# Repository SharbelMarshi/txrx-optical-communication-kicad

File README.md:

# A Free Space Optical Communication
This project implements a free-space optical communication link using two separate KiCad-designed boards: a transmitter and a receiver. The transmitter uses an RP2354A microcontroller to frame arbitrary digital payloads into packets and generate $100 \mathrm{kbit/s}$ RZ-OOK modulation for a $650 \mathrm{nm}$ laser module through a level-shifting buffer and an independent hardware safety chain.
The receiver uses a BPW34 photodiode, OPA320 transimpedance amplifier, and TLV3201 comparator to recover the optical pulses and feed them into an RP2354A for decoding, CRC verification, and delivery to the host system.
Both boards include USB-C, UART, SWD, a local $12 \mathrm{MHz}$ crystal, and a $10 \mathrm{MHz}$ SiTime SiT5346 DCTCXO reference. The SiT5346 is connected to the RP2354A through a GPIO/PIO clock input and is controllable over the existing $\text{I²C}$ bus. Each board also exposes a dedicated $1\mathrm{PPS}$ output generated by the RP2354A. The initial target is a stable free-space optical link over approximately $5$ meters.

## Architecture
Two separate $4$ layer boards:
- TX: RP2354A + USB-C + host I/O + $12 \mathrm{MHz}$ crystal + $10 \mathrm{MHz}$ SiT5346 DCTCXO + dedicated $1\mathrm{PPS}$ output + laser driver/safety chain + laser module.
- RX: RP2354A + USB-C + host I/O + $12 \mathrm{MHz}$ crystal + $10 \mathrm{MHz}$ SiT5346 DCTCXO + dedicated $1\mathrm{PPS}$ output + BPW34 / OPA320 / TLV3201 optical receiver + ADC monitor.

### TX
- TX_ROOT
- TX_POWER_USB
- TX_MCU_CLOCK
- TX_HOST_IO
- TX_LASER

### RX
- RX_ROOT
- RX_POWER_USB
- RX_MCU_CLOCK
- RX_HOST_IO
- RX_OPTICAL_AFE
- RX_MONITOR

### TX schamtics:

### TX PCB: 

### RX schamtics:

### RX PCB: 

## Library:
### Pre-built Components Compatibility Verfication:

Verified: Symbol and Footprint compatibility: 

1. RP2354A  ✓
2. AP2112K-3.3  ✓
3. SN74AHCT1G125DBVR  ✓
4. TPS22919DCKR  ✓
5. USBLC6-2SC6  ✓
7. REF2033  ✓

### Costum Components:

1. SiT5346 ✓
2. OPA320  ✓
3. TLV3201 ✓
4. BPW34 (custom footprint)  ✓
5. TPS7A2033  (customed symbol) ✓
6. ABM8-272-T3_3225 (custom footprint)  ✓
7. AOTA-B201610S3R3-101-T (custom footprint) ✓
8. ES22MCBE (custom footprint) ✓
9. B3B-PH-K-S ✓
10. B8B-PH-K-S ✓
11. ARD-LASER-MDI650-1-5 ✓
12. FTSH-105-01-L-DV-K ✓
13. USB4105-GF-A ✓

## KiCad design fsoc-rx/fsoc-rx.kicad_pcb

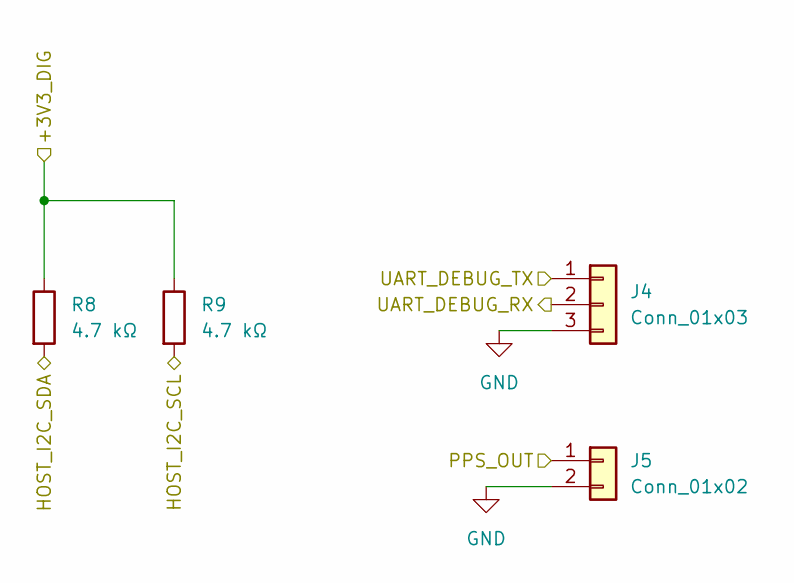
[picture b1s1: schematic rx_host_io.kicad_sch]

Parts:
J4: Conn_01x03; PinHeader_1x03_P2.54mm_Vertical
J5: Conn_01x02; PinHeader_1x02_P2.54mm_Vertical
R8, R9: 4.7 kΩ; R_0603_1608Metric

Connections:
/+3V3_DIG: R8.1, R9.1; also elsewhere on the board
/HOST_I2C_SCL: R9.2; also elsewhere on the board
/HOST_I2C_SDA: R8.2; also elsewhere on the board
/PPS_OUT: J5.1; also elsewhere on the board
/UART_DEBUG_RX: J4.2; also elsewhere on the board
/UART_DEBUG_TX: J4.1; also elsewhere on the board
GND: J4.3, J5.2; also elsewhere on the board

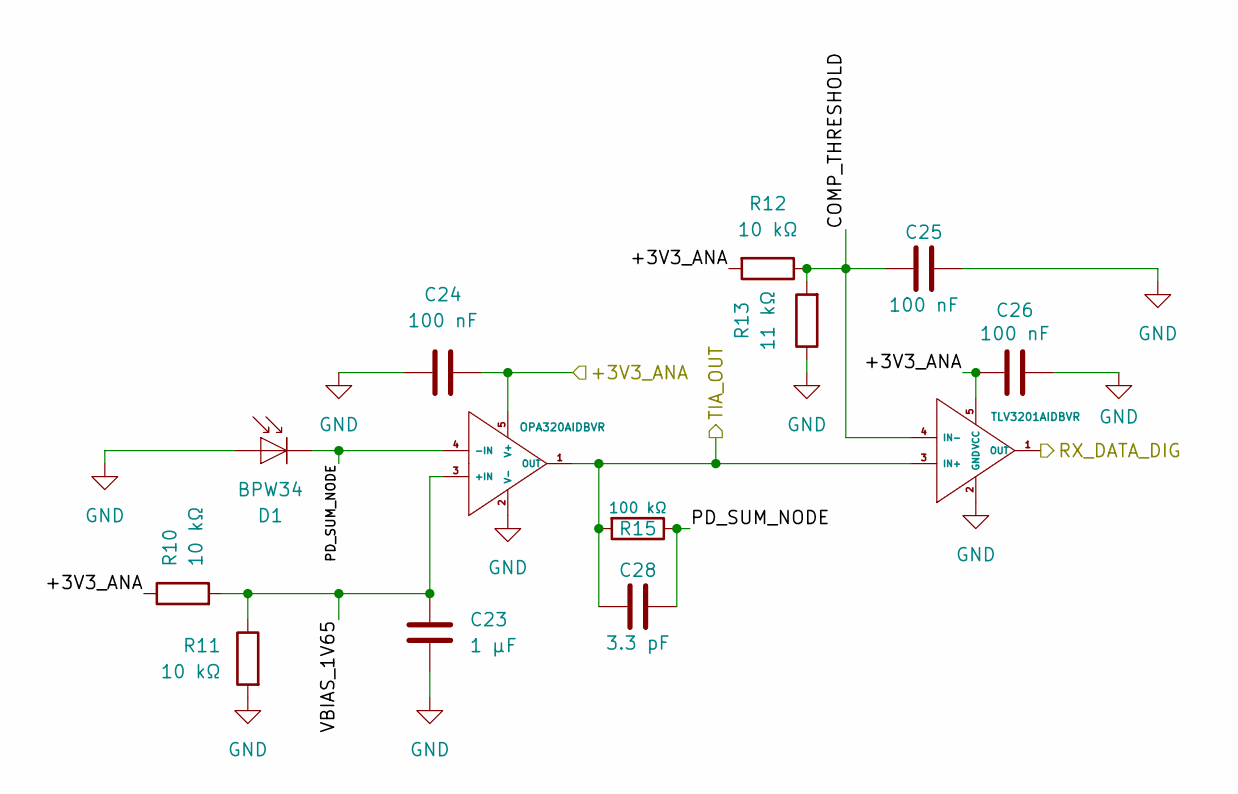
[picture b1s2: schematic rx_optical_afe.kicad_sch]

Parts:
C23: 1 µF; C_0805_2012Metric
C24, C25, C26: 100 nF; C_0603_1608Metric
C28: 3.3 pF; C_0603_1608Metric
D1: BPW34; BPW34_Vishay; MPN BPW34
R10, R11, R12: 10 kΩ; R_0603_1608Metric
R13: 11 kΩ; R_0603_1608Metric
R15: 100 kΩ; R_0603_1608Metric
U5: OPA320AIDBVR; SOT-23-5; MPN OPA320AIDBVR
U6: TLV3201AIDBVR; SOT-23-5; MPN TLV3201AIDBVR

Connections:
/+3V3_ANA: C24.2, C26.2, R10.1, R12.2, U5.5 (V+), U6.5 (VCC); also elsewhere on the board
/RX_DATA_DIG: U6.1 (OUT); also elsewhere on the board
/RX_OPTICAL_AFE/COMP_THRESHOLD: C25.1, R12.1, R13.2, U6.4 (IN-)
/RX_OPTICAL_AFE/PD_SUM_NODE: C28.2, D1.1 (K), R15.1, U5.4 (-IN)
/RX_OPTICAL_AFE/VBIAS_1V65: C23.1, R10.2, R11.1, U5.3 (+IN)
/TIA_OUT: C28.1, R15.2, U5.1 (OUT), U6.3 (IN+); also elsewhere on the board
GND: C23.2, C24.1, C25.2, C26.1, D1.2 (A), R11.2, R13.1, U5.2 (V-), U6.2 (GND); also elsewhere on the board

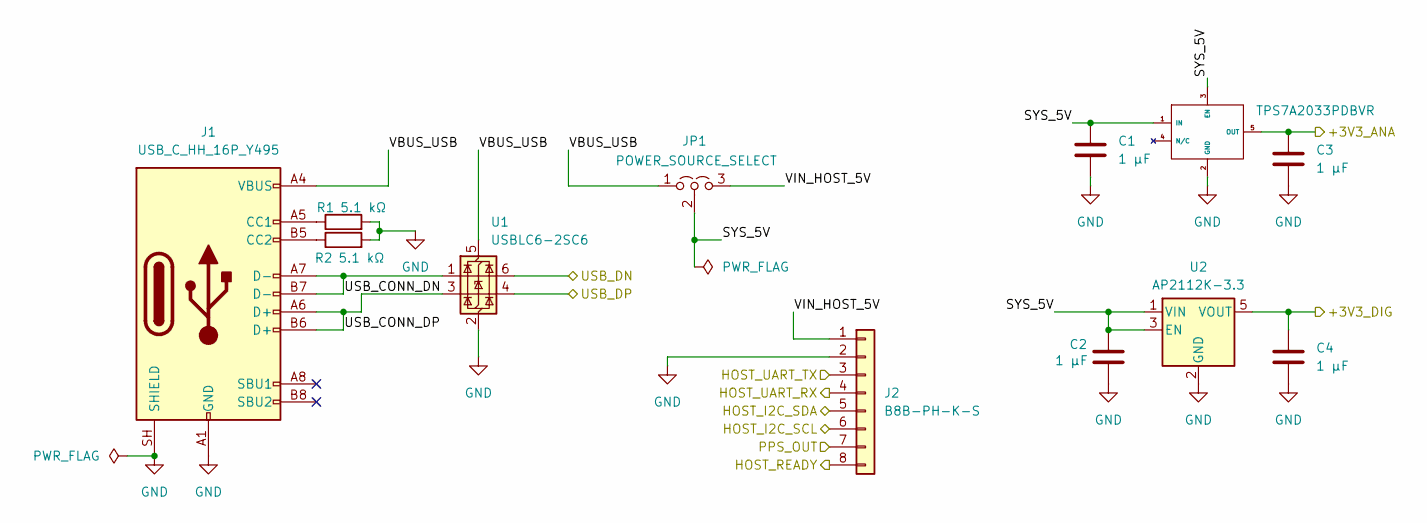
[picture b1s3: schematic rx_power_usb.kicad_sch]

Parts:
C1, C2, C3, C4: 1 µF; C_0805_2012Metric
J1: USB_C_HH_16P_Y495; MPN USB4105-GF-A
J2: B8B-PH-K-S; PinHeader_1x08_P2.54mm_Vertical; MPN B8B-PH-K-S
JP1: POWER_SOURCE_SELECT; PinHeader_1x03_P2.54mm_Vertical; MPN TSW-103-07-G-S
R1, R2: 5.1 kΩ; R_0603_1608Metric
U1: USBLC6-2SC6; SOT-23-6
U2: AP2112K-3.3; SOT-23-5
U3: TPS7A2033PDBVR; SOT-23-5; MPN TPS7A2033PDBVR

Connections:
/+3V3_ANA: C3.1, U3.5 (OUT); also elsewhere on the board
/+3V3_DIG: C4.1, U2.5 (VOUT); also elsewhere on the board
/HOST_I2C_SCL: J2.6; also elsewhere on the board
/HOST_I2C_SDA: J2.5; also elsewhere on the board
/HOST_READY: J2.8; also elsewhere on the board
/HOST_UART_RX: J2.4; also elsewhere on the board
/HOST_UART_TX: J2.3; also elsewhere on the board
/PPS_OUT: J2.7; also elsewhere on the board
/RX_POWER_USB/SYS_5V: C1.1, C2.1, JP1.2 (C), U2.1 (VIN), U2.3 (EN), U3.1 (IN), U3.3 (EN)
/RX_POWER_USB/USB_CONN_DN: J1.A7 (D-), J1.B7 (D-), U1.1 (I/O1)
/RX_POWER_USB/USB_CONN_DP: J1.A6 (D+), J1.B6 (D+), U1.3 (I/O2)
/RX_POWER_USB/VBUS_USB: J1.A4 (VBUS), J1.A9 (VBUS), J1.B4 (VBUS), J1.B9 (VBUS), JP1.1 (A), U1.5 (VBUS)
/RX_POWER_USB/VIN_HOST_5V: J2.1, JP1.3 (B)
/USB_DN: U1.6 (I/O1); also elsewhere on the board
/USB_DP: U1.4 (I/O2); also elsewhere on the board
GND: C1.2, C2.2, C3.2, C4.2, J1.A1 (GND), J1.A12 (GND), J1.B1 (GND), J1.B12 (GND), J1.SH (SHIELD), J2.2, R1.2, R2.2, U1.2 (GND), U2.2 (GND), U3.2 (GND); also elsewhere on the board
unnamed: J1.A5 (CC1), R1.1
unnamed: J1.B5 (CC2), R2.1

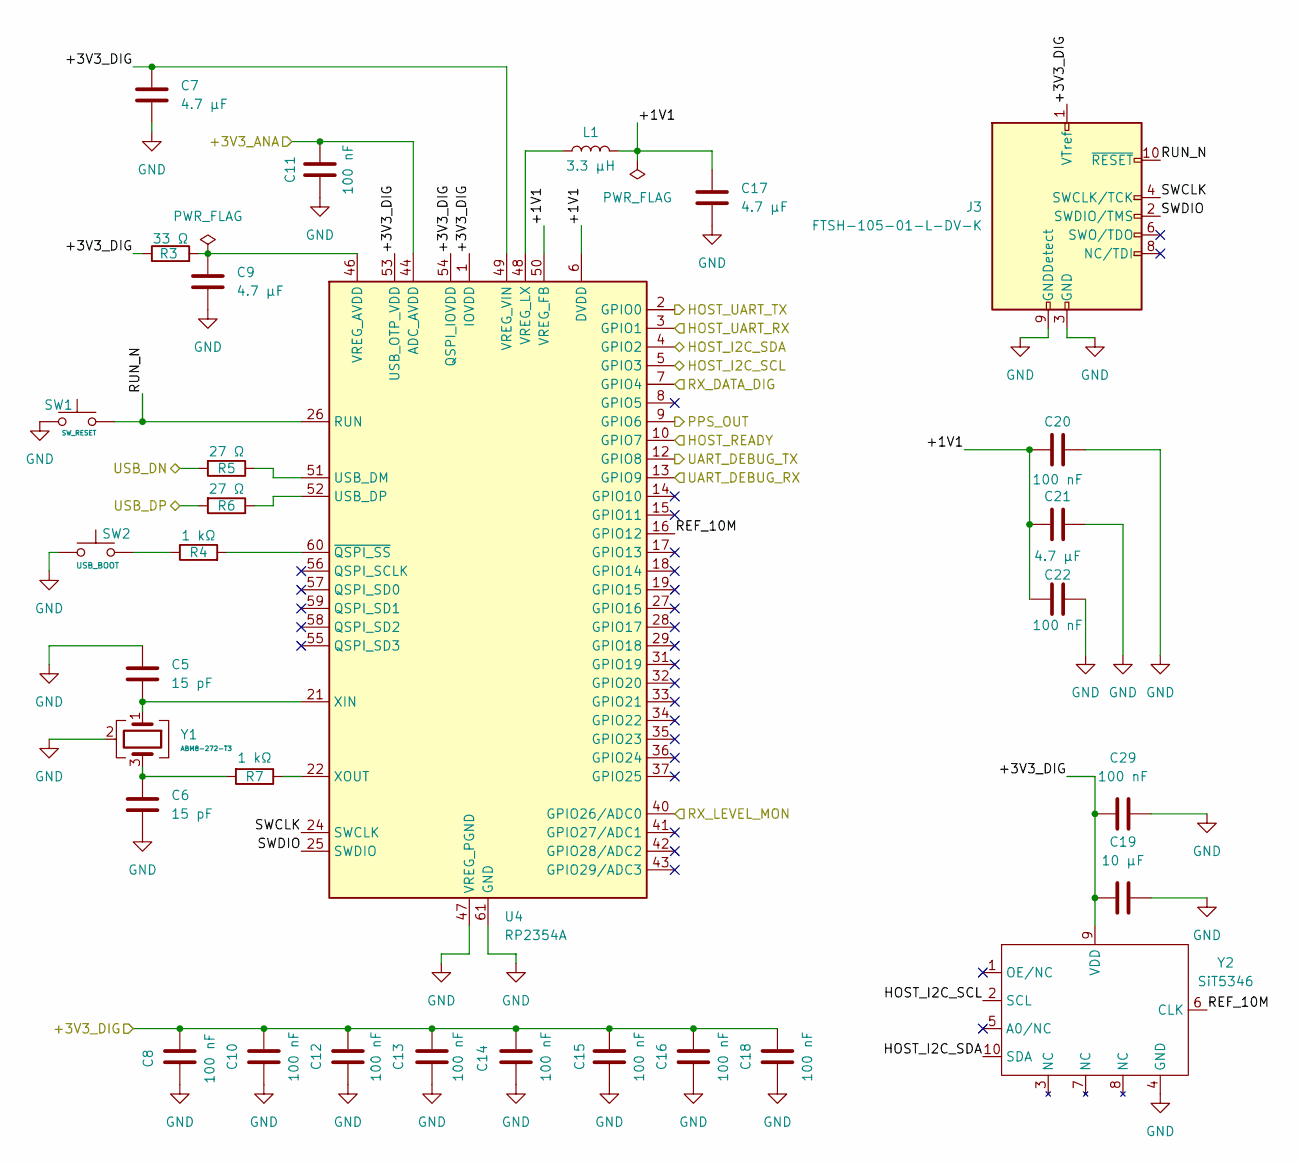
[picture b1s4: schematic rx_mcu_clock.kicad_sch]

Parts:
C5, C6: 15 pF; C_0603_1608Metric
C7, C9, C17, C21: 4.7 µF; C_0805_2012Metric
C8, C10, C11, C12, C13, C14, C15, C16, C18, C20, C22, C29: 100 nF; C_0603_1608Metric
C19: 10 µF; C_0805_2012Metric
J3: FTSH-105-01-L-DV-K; MPN FTSH-105-01-L-DV-K
L1: 3.3 µH; AOTA-B201610S3R3-101-T
R3: 33 Ω; R_0603_1608Metric
R4, R7: 1 kΩ; R_0603_1608Metric
R5, R6: 27 Ω; R_0603_1608Metric
SW1: SW_RESET; SW_SPST_PTS645Sx43SMTR92
SW2: USB_BOOT; SW_SPST_PTS645Sx43SMTR92
U4: RP2354A; RP2354A_ThermalVia_0p30
Y1: ABM8-272-T3; ABM8-272-T3_3225; MPN ABM8-272-T3
Y2: SiT5346; SiT5346_5.0x3.2mm_10L; MPN TBD - SiT5346 10MHz 3.3V LVCMOS DCTCXO; JLCPCB Part TBD - Global Sourcing if not stocked

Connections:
/+3V3_ANA: C11.2, U4.44 (ADC_AVDD); also elsewhere on the board
/+3V3_DIG: C7.1, C8.2, C10.2, C12.2, C13.2, C14.2, C15.2, C16.2, C18.2, C19.1, C29.1, J3.1 (VTref), R3.1, U4.1 (IOVDD), U4.11 (IOVDD), U4.20 (IOVDD), U4.30 (IOVDD), U4.38 (IOVDD), U4.45 (IOVDD), U4.49 (VREG_VIN), U4.53 (USB_OTP_VDD), U4.54 (QSPI_IOVDD), Y2.9 (VDD); also elsewhere on the board
/HOST_I2C_SCL: U4.5 (GPIO3), Y2.2 (SCL); also elsewhere on the board
/HOST_I2C_SDA: U4.4 (GPIO2), Y2.10 (SDA); also elsewhere on the board
/HOST_READY: U4.10 (GPIO7); also elsewhere on the board
/HOST_UART_RX: U4.3 (GPIO1); also elsewhere on the board
/HOST_UART_TX: U4.2 (GPIO0); also elsewhere on the board
/PPS_OUT: U4.9 (GPIO6); also elsewhere on the board
/RX_DATA_DIG: U4.7 (GPIO4); also elsewhere on the board
/RX_LEVEL_MON: U4.40 (GPIO26/ADC0); also elsewhere on the board
/RX_MCU_CLOCK/+1V1: C17.1, C20.1, C21.1, C22.2, L1.2, U4.6 (DVDD), U4.23 (DVDD), U4.39 (DVDD), U4.50 (VREG_FB)
/RX_MCU_CLOCK/REF_10M: U4.16 (GPIO12), Y2.6 (CLK)
/RX_MCU_CLOCK/RUN_N: J3.10 (~RESET), SW1.1, U4.26 (RUN)
/RX_MCU_CLOCK/SWCLK: J3.4 (SWCLK/TCK), U4.24 (SWCLK)
/RX_MCU_CLOCK/SWDIO: J3.2 (SWDIO/TMS), U4.25 (SWDIO)
/UART_DEBUG_RX: U4.13 (GPIO9); also elsewhere on the board
/UART_DEBUG_TX: U4.12 (GPIO8); also elsewhere on the board
/USB_DN: R5.2; also elsewhere on the board
/USB_DP: R6.2; also elsewhere on the board
GND: C5.1, C6.2, C7.2, C8.1, C9.2, C10.1, C11.1, C12.1, C13.1, C14.1, C15.1, C16.1, C17.2, C18.1, C19.2, C20.2, C21.2, C22.1, C29.2, J3.3 (GND), J3.5 (GND), J3.9 (GNDDetect), SW1.2, SW2.1, U4.47 (VREG_PGND), U4.61 (GND), Y1.2 (G), Y1.4 (G), Y2.4 (GND); also elsewhere on the board
unnamed: C6.1, R7.2, Y1.3
unnamed: R4.1, SW2.2
unnamed: R5.1, U4.51 (USB_DM)
unnamed: R6.1, U4.52 (USB_DP)
unnamed: C9.1, R3.2, U4.46 (VREG_AVDD)
unnamed: L1.1, U4.48 (VREG_LX)
unnamed: C5.2, U4.21 (XIN), Y1.1
unnamed: R7.1, U4.22 (XOUT)
unnamed: R4.2, U4.60 (~QSPI_SS)

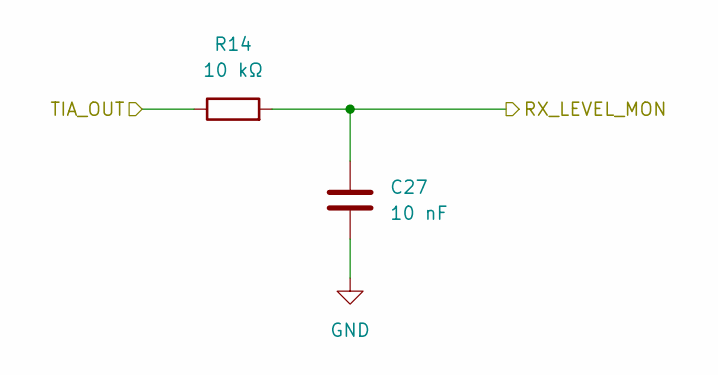
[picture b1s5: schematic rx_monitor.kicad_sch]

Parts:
C27: 10 nF; C_0603_1608Metric
R14: 10 kΩ; R_0603_1608Metric

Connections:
/RX_LEVEL_MON: C27.1, R14.2; also elsewhere on the board
/TIA_OUT: R14.1; also elsewhere on the board
GND: C27.2; also elsewhere on the board

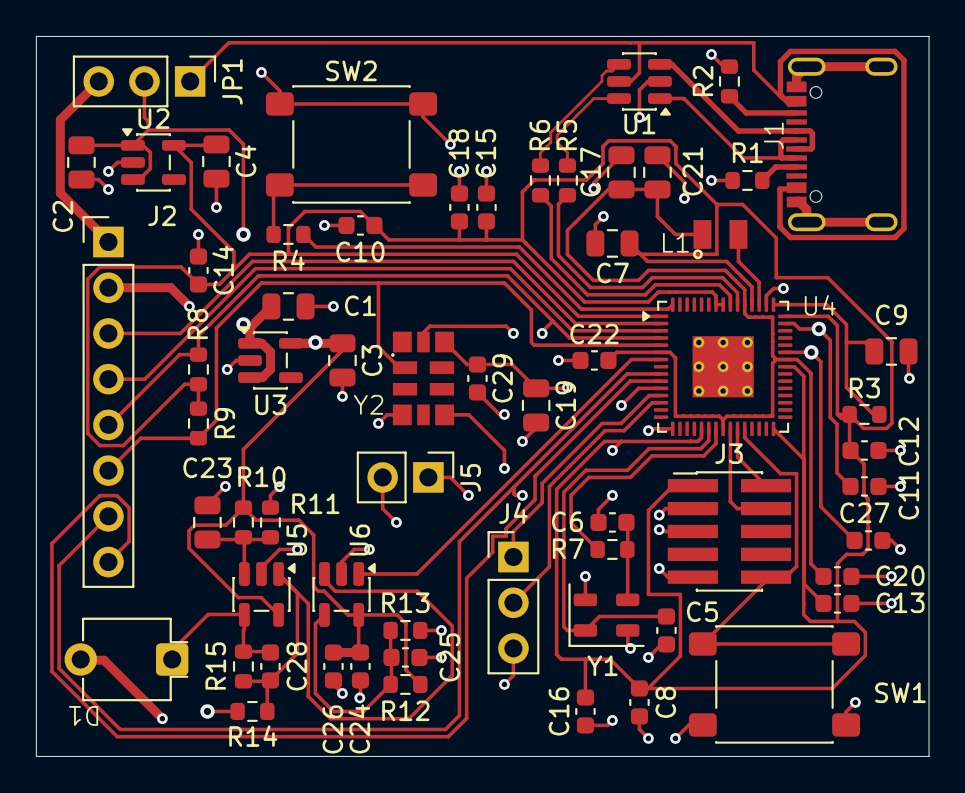
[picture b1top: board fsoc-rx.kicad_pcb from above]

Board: 4 copper layers, 49.6 x 40.0 mm, 62 parts (0 on the bottom side), 40 nets.

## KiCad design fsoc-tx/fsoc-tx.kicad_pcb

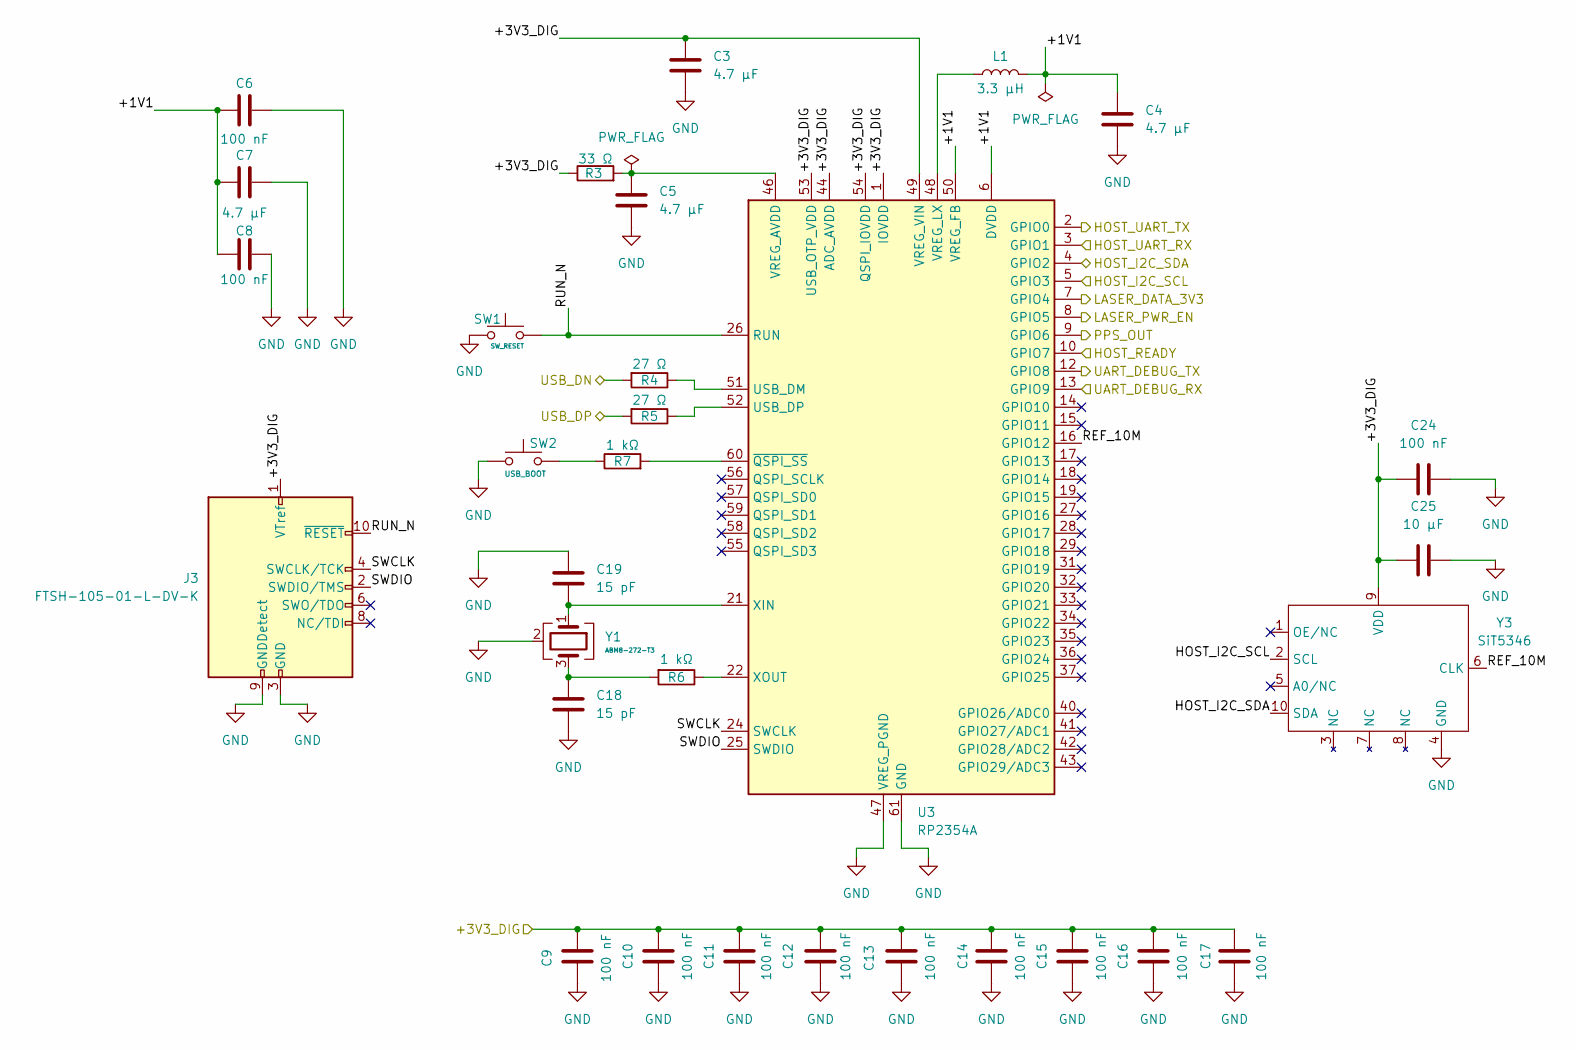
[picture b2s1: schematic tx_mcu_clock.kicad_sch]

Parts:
C3, C4, C5, C7: 4.7 µF; C_0805_2012Metric
C6, C8, C9, C10, C11, C12, C13, C14, C15, C16, C17, C24: 100 nF; C_0603_1608Metric
C18, C19: 15 pF; C_0603_1608Metric
C25: 10 µF; C_0805_2012Metric
J3: FTSH-105-01-L-DV-K; MPN FTSH-105-01-L-DV-K
L1: 3.3 µH; AOTA-B201610S3R3-101-T
R3: 33 Ω; R_0603_1608Metric
R4, R5: 27 Ω; R_0603_1608Metric
R6, R7: 1 kΩ; R_0603_1608Metric
SW1: SW_RESET; SW_SPST_PTS645Sx43SMTR92
SW2: USB_BOOT; SW_SPST_PTS645Sx43SMTR92
U3: RP2354A; RP2354A_ThermalVia_0p30
Y1: ABM8-272-T3; ABM8-272-T3_3225; MPN ABM8-272-T3
Y3: SiT5346; SiT5346_5.0x3.2mm_10L; MPN TBD - SiT5346 10MHz 3.3V LVCMOS DCTCXO; JLCPCB Part TBD - Global Sourcing if not stocked

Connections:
/+3V3_DIG: C3.1, C9.2, C10.2, C11.2, C12.2, C13.2, C14.2, C15.2, C16.2, C17.2, C24.1, C25.1, J3.1 (VTref), R3.1, U3.1 (IOVDD), U3.11 (IOVDD), U3.20 (IOVDD), U3.30 (IOVDD), U3.38 (IOVDD), U3.44 (ADC_AVDD), U3.45 (IOVDD), U3.49 (VREG_VIN), U3.53 (USB_OTP_VDD), U3.54 (QSPI_IOVDD), Y3.9 (VDD); also elsewhere on the board
/HOST_I2C_SCL: U3.5 (GPIO3), Y3.2 (SCL); also elsewhere on the board
/HOST_I2C_SDA: U3.4 (GPIO2), Y3.10 (SDA); also elsewhere on the board
/HOST_READY: U3.10 (GPIO7); also elsewhere on the board
/HOST_UART_RX: U3.3 (GPIO1); also elsewhere on the board
/HOST_UART_TX: U3.2 (GPIO0); also elsewhere on the board
/LASER_DATA_3V3: U3.7 (GPIO4); also elsewhere on the board
/LASER_PWR_EN: U3.8 (GPIO5); also elsewhere on the board
/PPS_OUT: U3.9 (GPIO6); also elsewhere on the board
/TX_MCU_CLOCK/+1V1: C4.1, C6.1, C7.1, C8.2, L1.2, U3.6 (DVDD), U3.23 (DVDD), U3.39 (DVDD), U3.50 (VREG_FB)
/TX_MCU_CLOCK/REF_10M: U3.16 (GPIO12), Y3.6 (CLK)
/TX_MCU_CLOCK/RUN_N: J3.10 (~RESET), SW1.1, U3.26 (RUN)
/TX_MCU_CLOCK/SWCLK: J3.4 (SWCLK/TCK), U3.24 (SWCLK)
/TX_MCU_CLOCK/SWDIO: J3.2 (SWDIO/TMS), U3.25 (SWDIO)
/UART_DEBUG_RX: U3.13 (GPIO9); also elsewhere on the board
/UART_DEBUG_TX: U3.12 (GPIO8); also elsewhere on the board
/USB_DN: R4.2; also elsewhere on the board
/USB_DP: R5.2; also elsewhere on the board
GND: C3.2, C4.2, C5.2, C6.2, C7.2, C8.1, C9.1, C10.1, C11.1, C12.1, C13.1, C14.1, C15.1, C16.1, C17.1, C18.2, C19.1, C24.2, C25.2, J3.3 (GND), J3.5 (GND), J3.9 (GNDDetect), SW1.2, SW2.1, U3.47 (VREG_PGND), U3.61 (GND), Y1.2 (G), Y1.4 (G), Y3.4 (GND); also elsewhere on the board
unnamed: C18.1, R6.2, Y1.3
unnamed: R7.1, SW2.2
unnamed: R4.1, U3.51 (USB_DM)
unnamed: R5.1, U3.52 (USB_DP)
unnamed: C5.1, R3.2, U3.46 (VREG_AVDD)
unnamed: L1.1, U3.48 (VREG_LX)
unnamed: C19.2, U3.21 (XIN), Y1.1
unnamed: R6.1, U3.22 (XOUT)
unnamed: R7.2, U3.60 (~QSPI_SS)

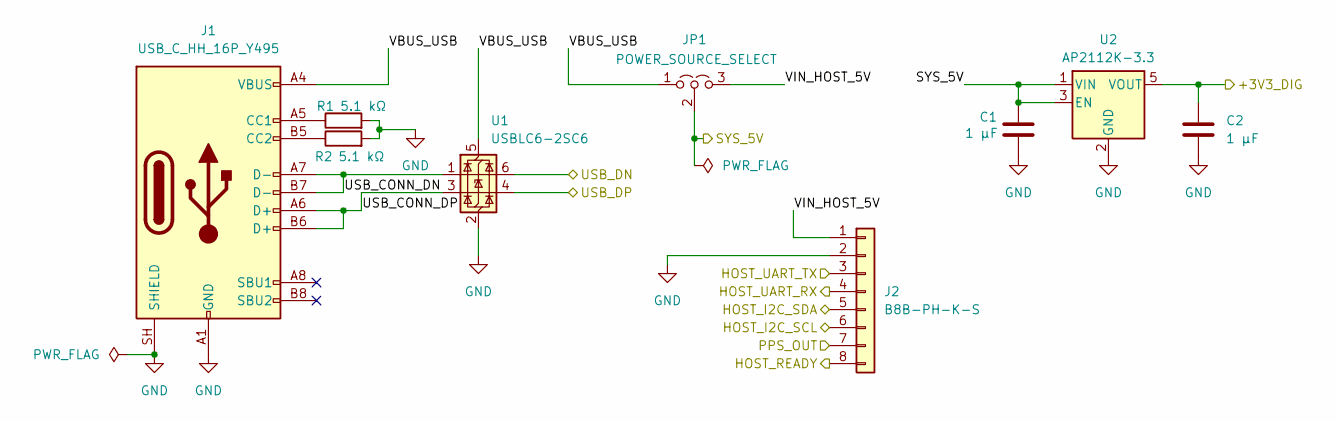
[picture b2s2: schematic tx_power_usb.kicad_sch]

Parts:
C1, C2: 1 µF; C_0805_2012Metric
J1: USB_C_HH_16P_Y495; MPN USB4105-GF-A
J2: B8B-PH-K-S; PinHeader_1x08_P2.54mm_Vertical; MPN B8B-PH-K-S
JP1: POWER_SOURCE_SELECT; PinHeader_1x03_P2.54mm_Vertical; MPN TSW-103-07-G-S
R1, R2: 5.1 kΩ; R_0603_1608Metric
U1: USBLC6-2SC6; SOT-23-6
U2: AP2112K-3.3; SOT-23-5

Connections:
/+3V3_DIG: C2.1, U2.5 (VOUT); also elsewhere on the board
/HOST_I2C_SCL: J2.6; also elsewhere on the board
/HOST_I2C_SDA: J2.5; also elsewhere on the board
/HOST_READY: J2.8; also elsewhere on the board
/HOST_UART_RX: J2.4; also elsewhere on the board
/HOST_UART_TX: J2.3; also elsewhere on the board
/PPS_OUT: J2.7; also elsewhere on the board
/SYS_5V: C1.1, JP1.2 (C), U2.1 (VIN), U2.3 (EN); also elsewhere on the board
/TX_POWER_USB/USB_CONN_DN: J1.A7 (D-), J1.B7 (D-), U1.1 (I/O1)
/TX_POWER_USB/USB_CONN_DP: J1.A6 (D+), J1.B6 (D+), U1.3 (I/O2)
/TX_POWER_USB/VBUS_USB: J1.A4 (VBUS), J1.A9 (VBUS), J1.B4 (VBUS), J1.B9 (VBUS), JP1.1 (A), U1.5 (VBUS)
/TX_POWER_USB/VIN_HOST_5V: J2.1, JP1.3 (B)
/USB_DN: U1.6 (I/O1); also elsewhere on the board
/USB_DP: U1.4 (I/O2); also elsewhere on the board
GND: C1.2, C2.2, J1.A1 (GND), J1.A12 (GND), J1.B1 (GND), J1.B12 (GND), J1.SH (SHIELD), J2.2, R1.2, R2.2, U1.2 (GND), U2.2 (GND); also elsewhere on the board
unnamed: J1.A5 (CC1), R1.1
unnamed: J1.B5 (CC2), R2.1

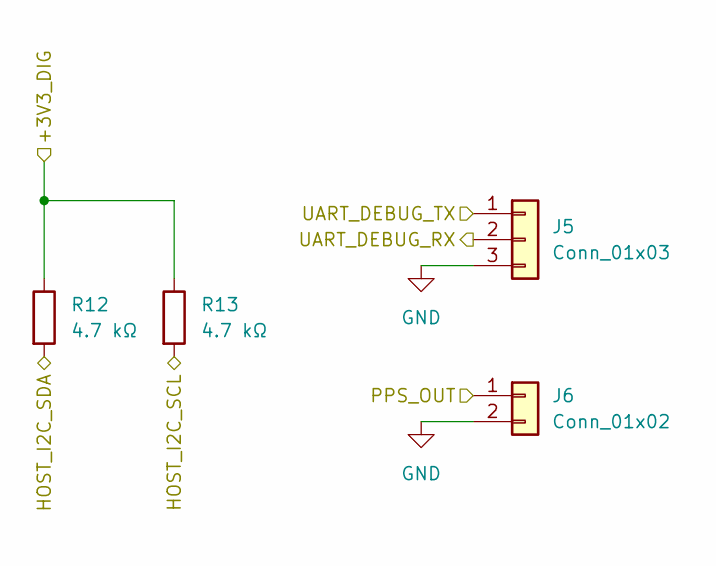
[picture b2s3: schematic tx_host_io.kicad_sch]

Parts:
J5: Conn_01x03; PinHeader_1x03_P2.54mm_Vertical
J6: Conn_01x02; PinHeader_1x02_P2.54mm_Vertical
R12, R13: 4.7 kΩ; R_0603_1608Metric

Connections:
/+3V3_DIG: R12.1, R13.1; also elsewhere on the board
/HOST_I2C_SCL: R13.2; also elsewhere on the board
/HOST_I2C_SDA: R12.2; also elsewhere on the board
/PPS_OUT: J6.1; also elsewhere on the board
/UART_DEBUG_RX: J5.2; also elsewhere on the board
/UART_DEBUG_TX: J5.1; also elsewhere on the board
GND: J5.3, J6.2; also elsewhere on the board

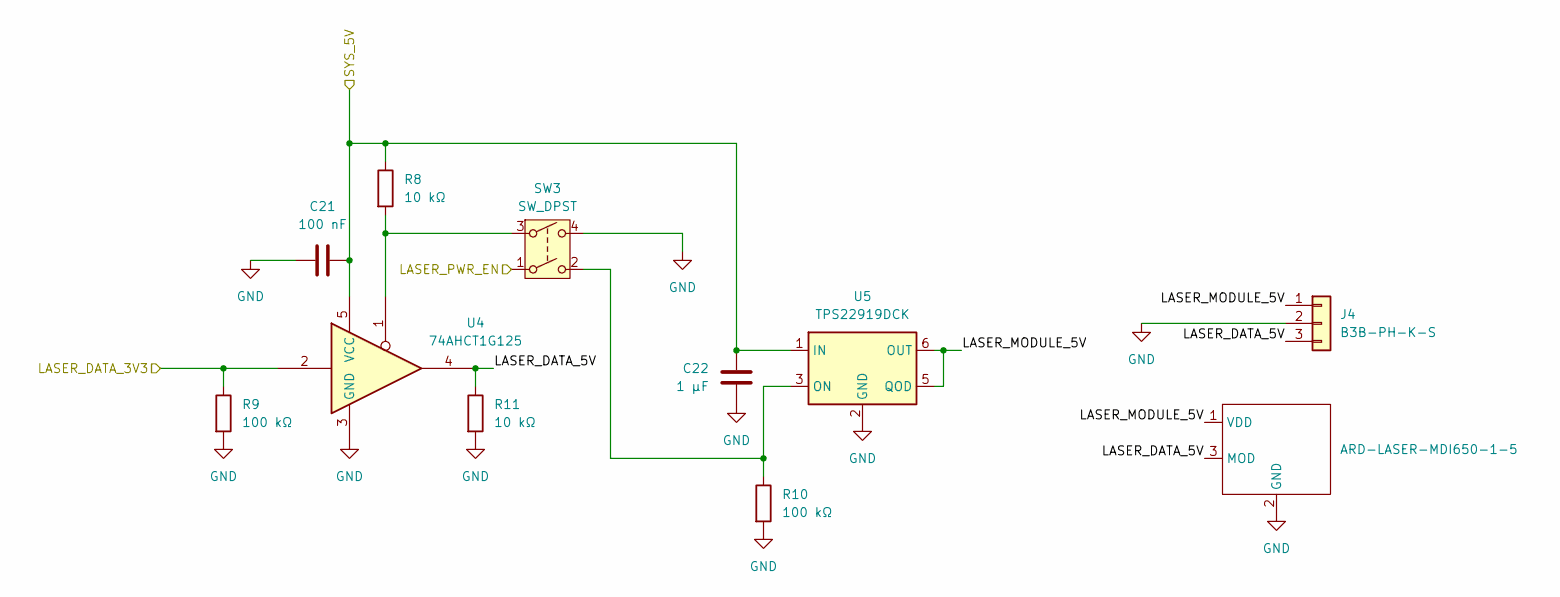
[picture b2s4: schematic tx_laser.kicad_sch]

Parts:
C21: 100 nF; C_0603_1608Metric
C22: 1 µF; C_0805_2012Metric
J4: B3B-PH-K-S; PinHeader_1x03_P2.54mm_Vertical; MPN B3B-PH-K-S
MOD1: ARD-LASER-MDI650-1-5; MPN ARD-LASER-MDI650-1-5(10x26)
R8, R11: 10 kΩ; R_0603_1608Metric
R9, R10: 100 kΩ; R_0603_1608Metric
SW3: SW_DPST; ES22MCBE
U4: 74AHCT1G125; SOT-23-5
U5: TPS22919DCK; SOT-363_SC-70-6

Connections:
/LASER_DATA_3V3: R9.1, U4.2; also elsewhere on the board
/LASER_PWR_EN: SW3.1; also elsewhere on the board
/SYS_5V: C21.2, C22.1, R8.1, U4.5 (VCC), U5.1 (IN); also elsewhere on the board
/TX_LASER/LASER_DATA_5V: J4.3, MOD1.3 (MOD), R11.1, U4.4
/TX_LASER/LASER_MODULE_5V: J4.1, MOD1.1 (VDD), U5.5 (QOD), U5.6 (OUT)
GND: C21.1, C22.2, J4.2, MOD1.2 (GND), R9.2, R10.2, R11.2, SW3.4, U4.3 (GND), U5.2 (GND); also elsewhere on the board
unnamed: R8.2, SW3.3, U4.1
unnamed: R10.1, SW3.2, U5.3 (ON)

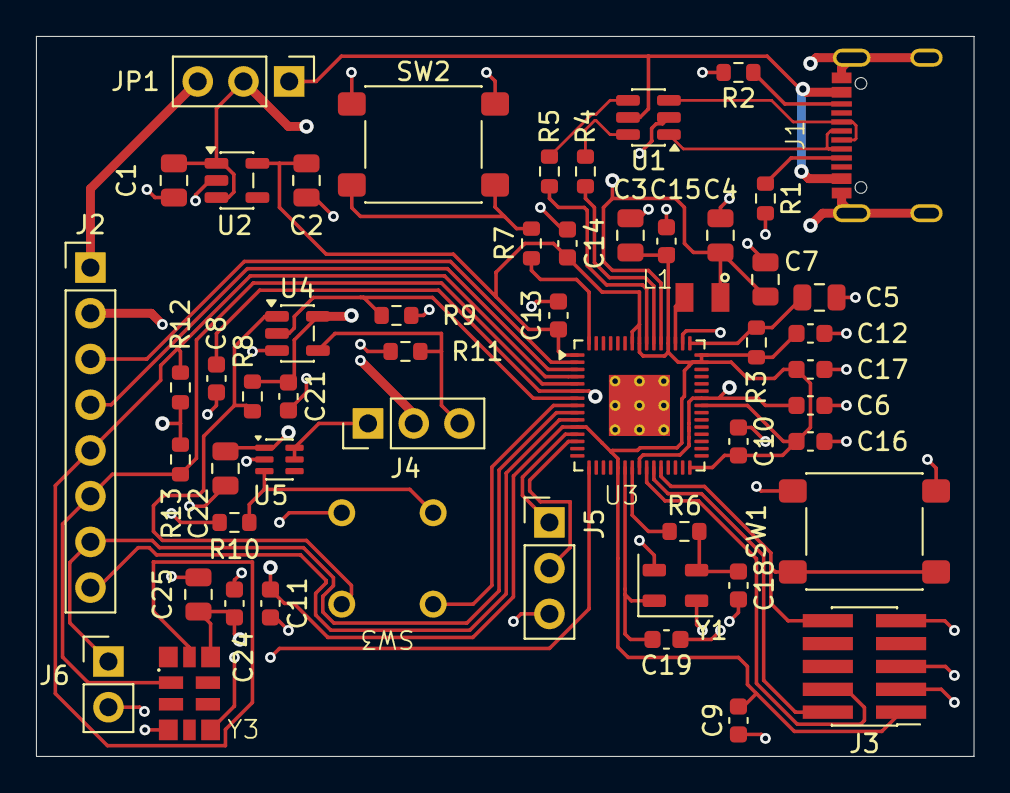
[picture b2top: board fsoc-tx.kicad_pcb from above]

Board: 4 copper layers, 52.1 x 40.0 mm, 54 parts (0 on the bottom side), 39 nets.
